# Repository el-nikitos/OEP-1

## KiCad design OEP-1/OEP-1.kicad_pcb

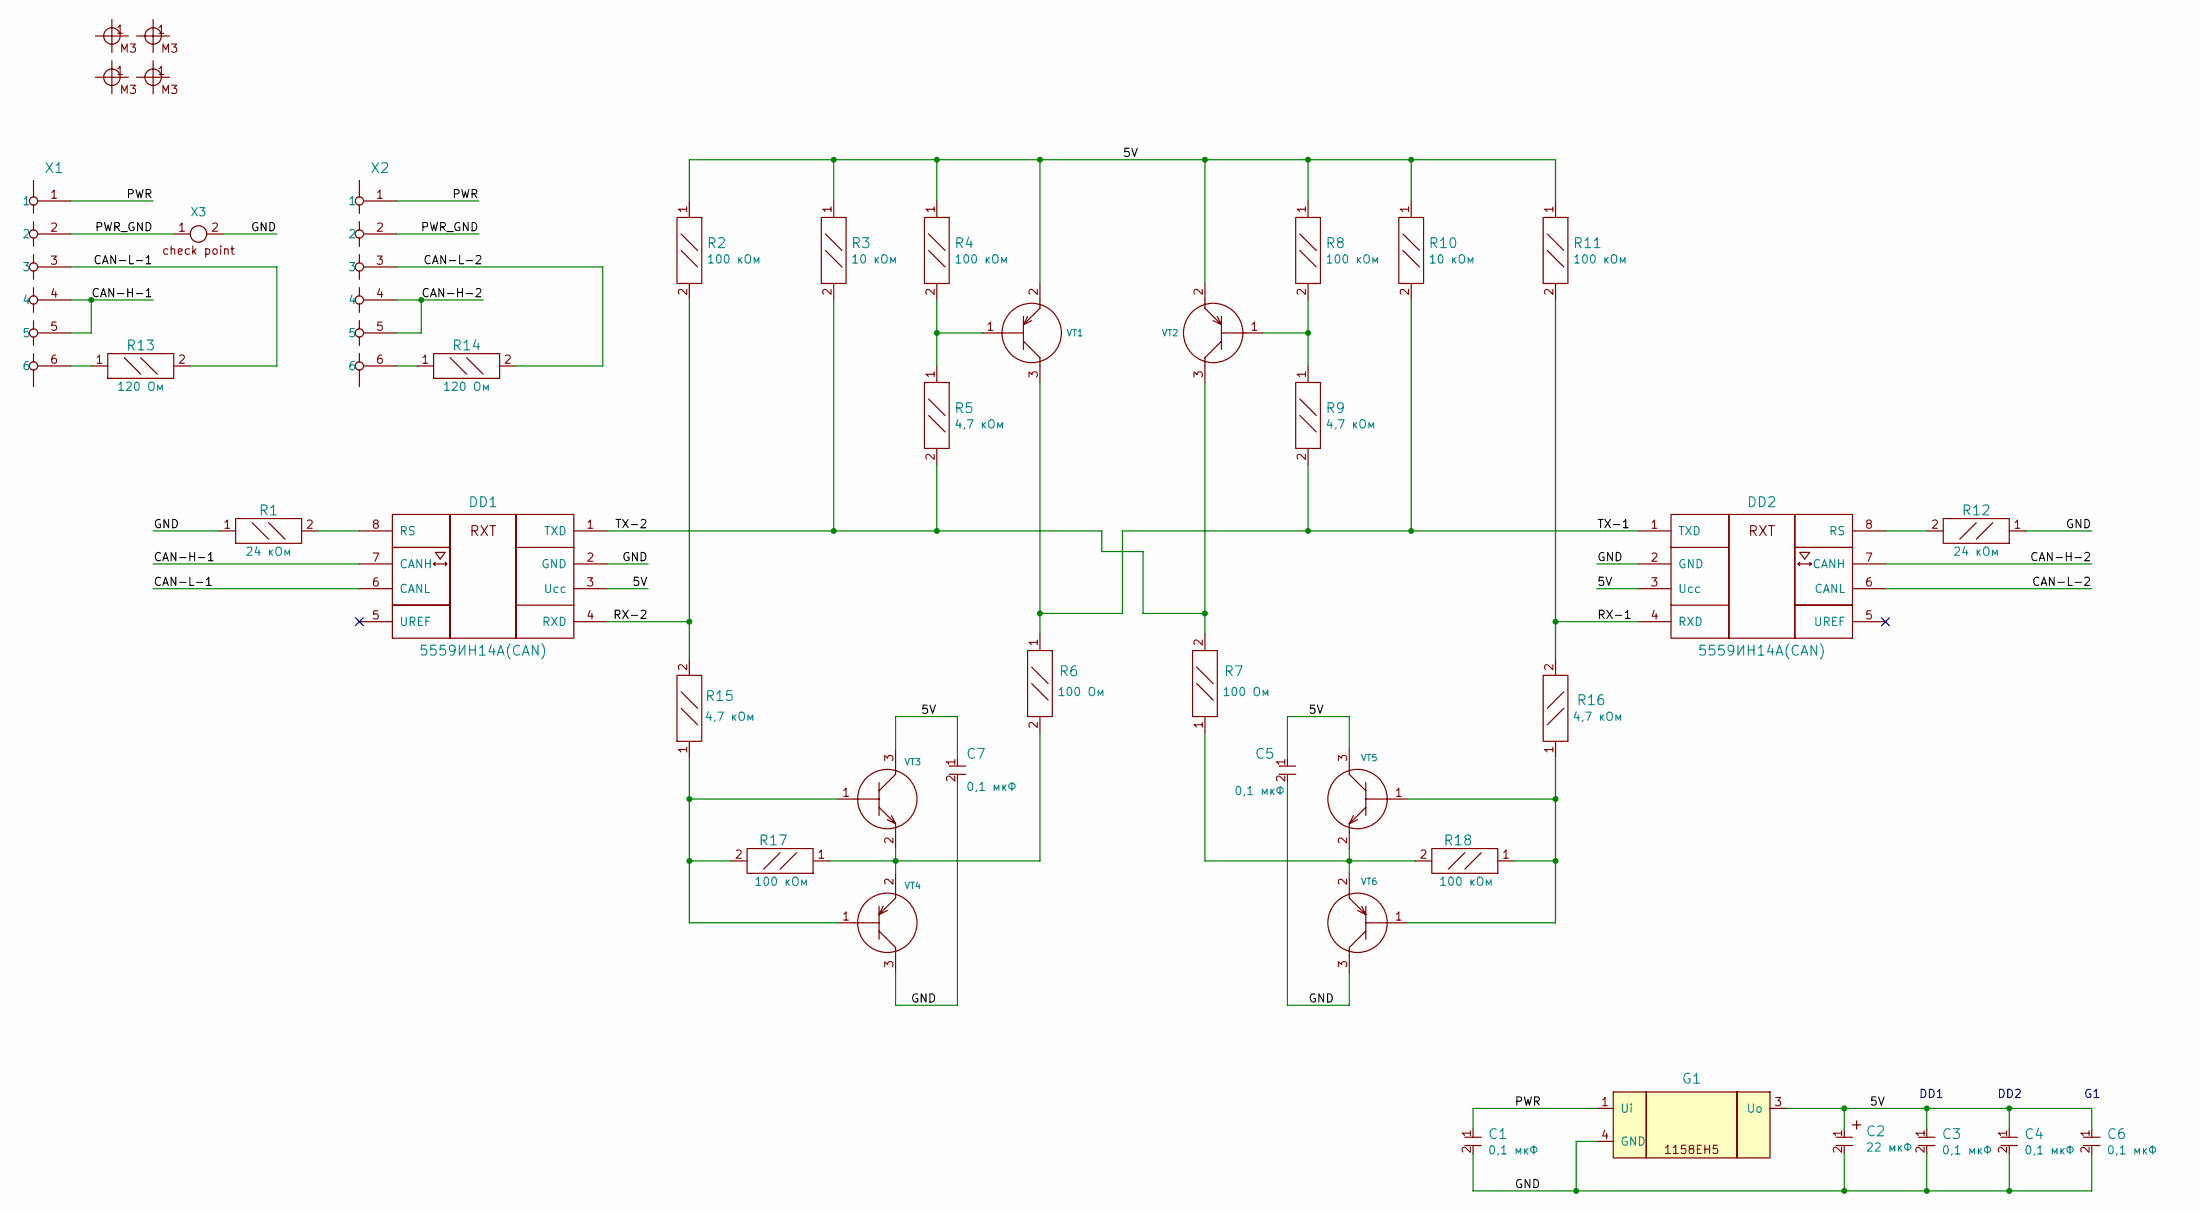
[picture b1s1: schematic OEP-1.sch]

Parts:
C1, C3, C4, C5, C6, C7: Конденсатор_К10-83-25В-0,1_мкФ+-20проц.; Конденсатор_SMD_IEC_0805
C2: Конденсатор_К53-56А-32В-22_мкФ+-10проц.; Конденсатор_тантал_SMD_m7343
DD1, DD2: 5559ИН14А(CAN); SO-8
G1: Микросхема_интегральная_КФ1158ЕН501А; TO_252___KF1158EN3_301A
R1, R2, R3, R4, R5, R6, R7, R8, R9, R10, R11, R12, R13, R14, R15, R16, R17, R18: Резистор_0,125Вт; Резистор_SMD_IEC_0805_0,125_Вт
VT1, VT2, VT4, VT6: Транзистор_2Т3129Г9; Корпус_КТ-46
VT3, VT5: Транзистор_2Т3130А9; Корпус_КТ-46
X1, X2: Клеммник_х6; Вилка_СНП389-6ВП32-1-1
X3: Контрольная_точка_сопряжения; Пробник
X4, X5, X6, X7: Крепежное_отверстие_М3; Крепежное_Отверстие_под_М3

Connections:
/5V: C2.1, C3.1, C4.1, C5.1, C6.1, C7.1, DD1.3 (Ucc), DD2.3 (Ucc), G1.3 (Uo), R2.1, R3.1, R4.1, R8.1, R10.1, R11.1, VT1.2, VT2.2, VT3.3, VT5.3
/CAN-H-1: DD1.7 (CANH), X1.4, X1.5
/CAN-H-2: DD2.7 (CANH), X2.4, X2.5
/CAN-L-1: DD1.6 (CANL), R13.2, X1.3
/CAN-L-2: DD2.6 (CANL), R14.2, X2.3
/GND: C1.2, C2.2, C3.2, C4.2, C5.2, C6.2, C7.2, DD1.2 (GND), DD2.2 (GND), G1.4 (GND), R1.1, R12.1, VT4.3, VT6.3, X3.2
/PWR: C1.1, G1.1 (Ui), X1.1, X2.1
/PWR_GND: X1.2, X2.2, X3.1
/RX-1: DD2.4 (RXD), R11.2, R16.2
/RX-2: DD1.4 (RXD), R2.2, R15.2
/TX-1: DD2.1 (TXD), R6.1, R9.2, R10.2, VT1.3
/TX-2: DD1.1 (TXD), R3.2, R5.2, R7.2, VT2.3
unnamed: DD1.8 (RS), R1.2
unnamed: DD2.8 (RS), R12.2
unnamed: R4.2, R5.1, VT1.1
unnamed: R8.2, R9.1, VT2.1
unnamed: R13.1, X1.6
unnamed: R14.1, X2.6
unnamed: R15.1, R17.2, VT3.1, VT4.1
unnamed: R16.1, R18.1, VT5.1, VT6.1
unnamed: R6.2, R17.1, VT3.2, VT4.2
unnamed: R7.1, R18.2, VT5.2, VT6.2

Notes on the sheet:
DD1
DD2

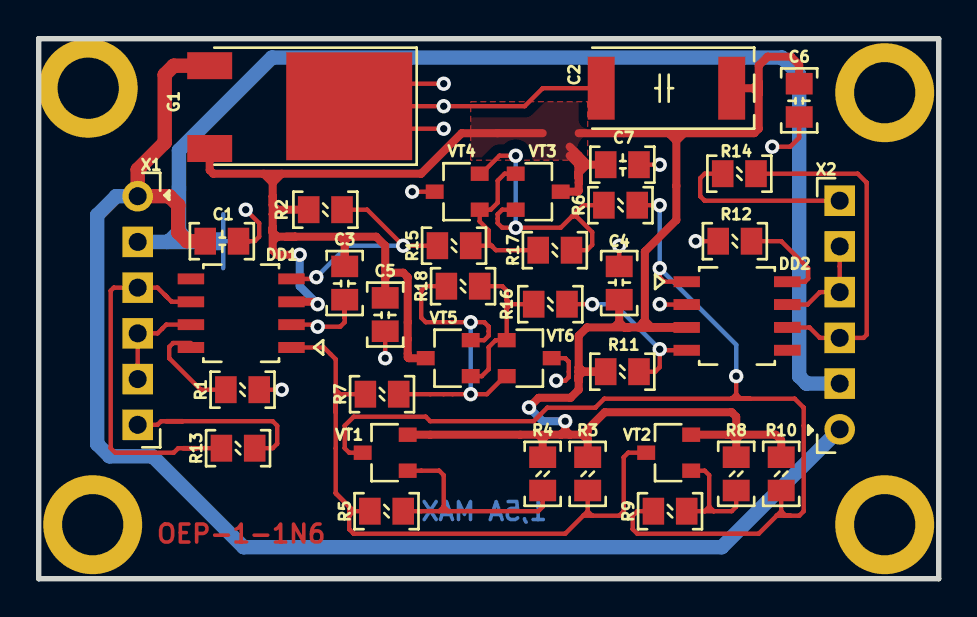
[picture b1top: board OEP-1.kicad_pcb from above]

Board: 2 copper layers, 50.0 x 30.0 mm, 41 parts (1 on the bottom side), 22 nets.

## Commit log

2021-06-04 заготовка для DIO-CAN
2021-06-05 подготовлена схема повторителя, надо добавить PCB клеммников+трассировка
2021-06-06 готова трассировка, подготовлены файлы производства (45х30)мм)
2021-06-22 ОУ заменен на транзисторный каскад (50х30 мм)
2021-06-24 причесана трассировка, добавлены gerber-файлы
